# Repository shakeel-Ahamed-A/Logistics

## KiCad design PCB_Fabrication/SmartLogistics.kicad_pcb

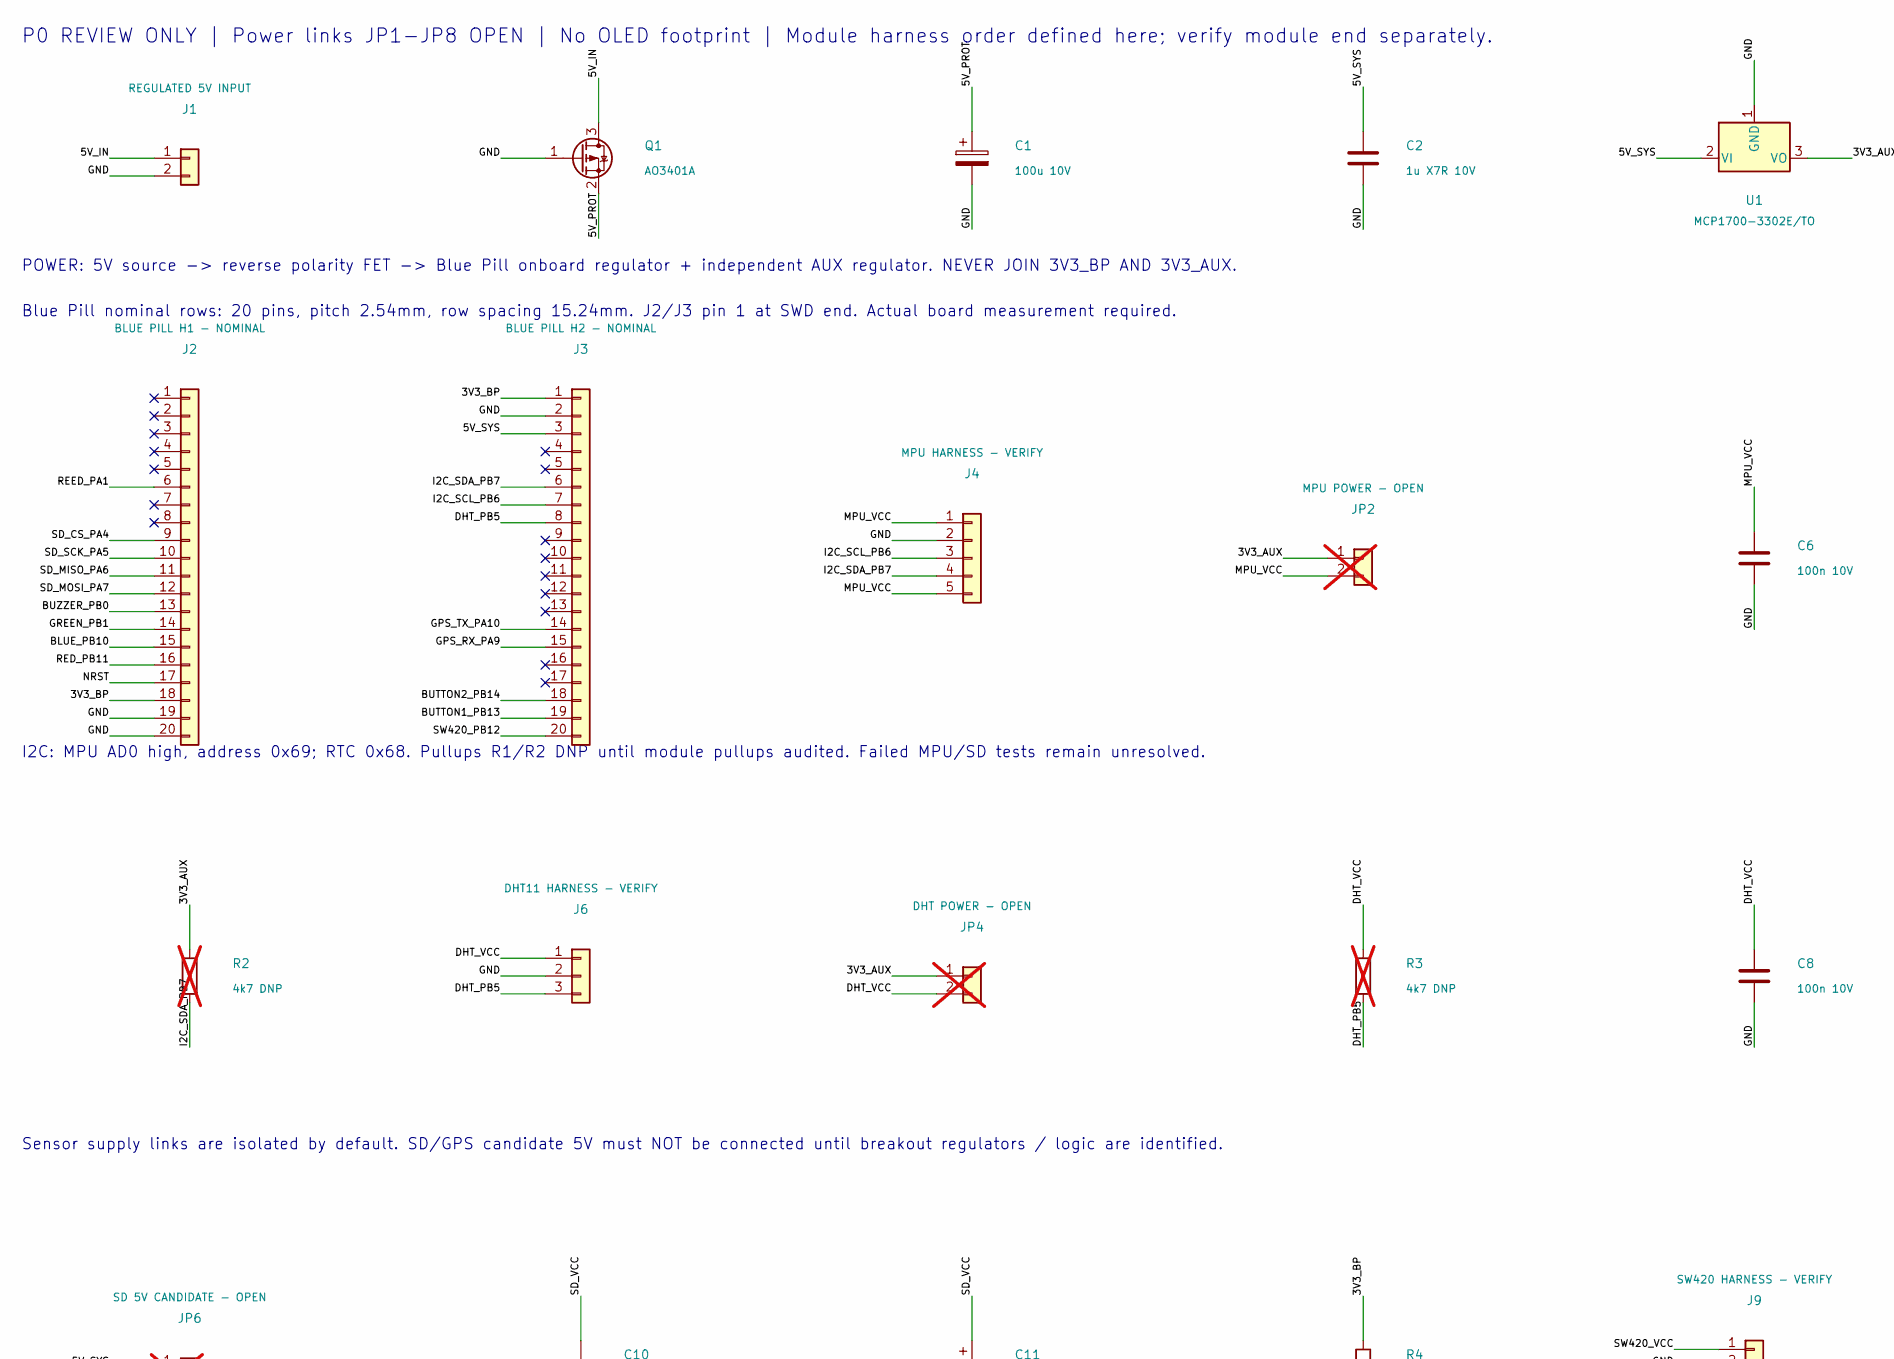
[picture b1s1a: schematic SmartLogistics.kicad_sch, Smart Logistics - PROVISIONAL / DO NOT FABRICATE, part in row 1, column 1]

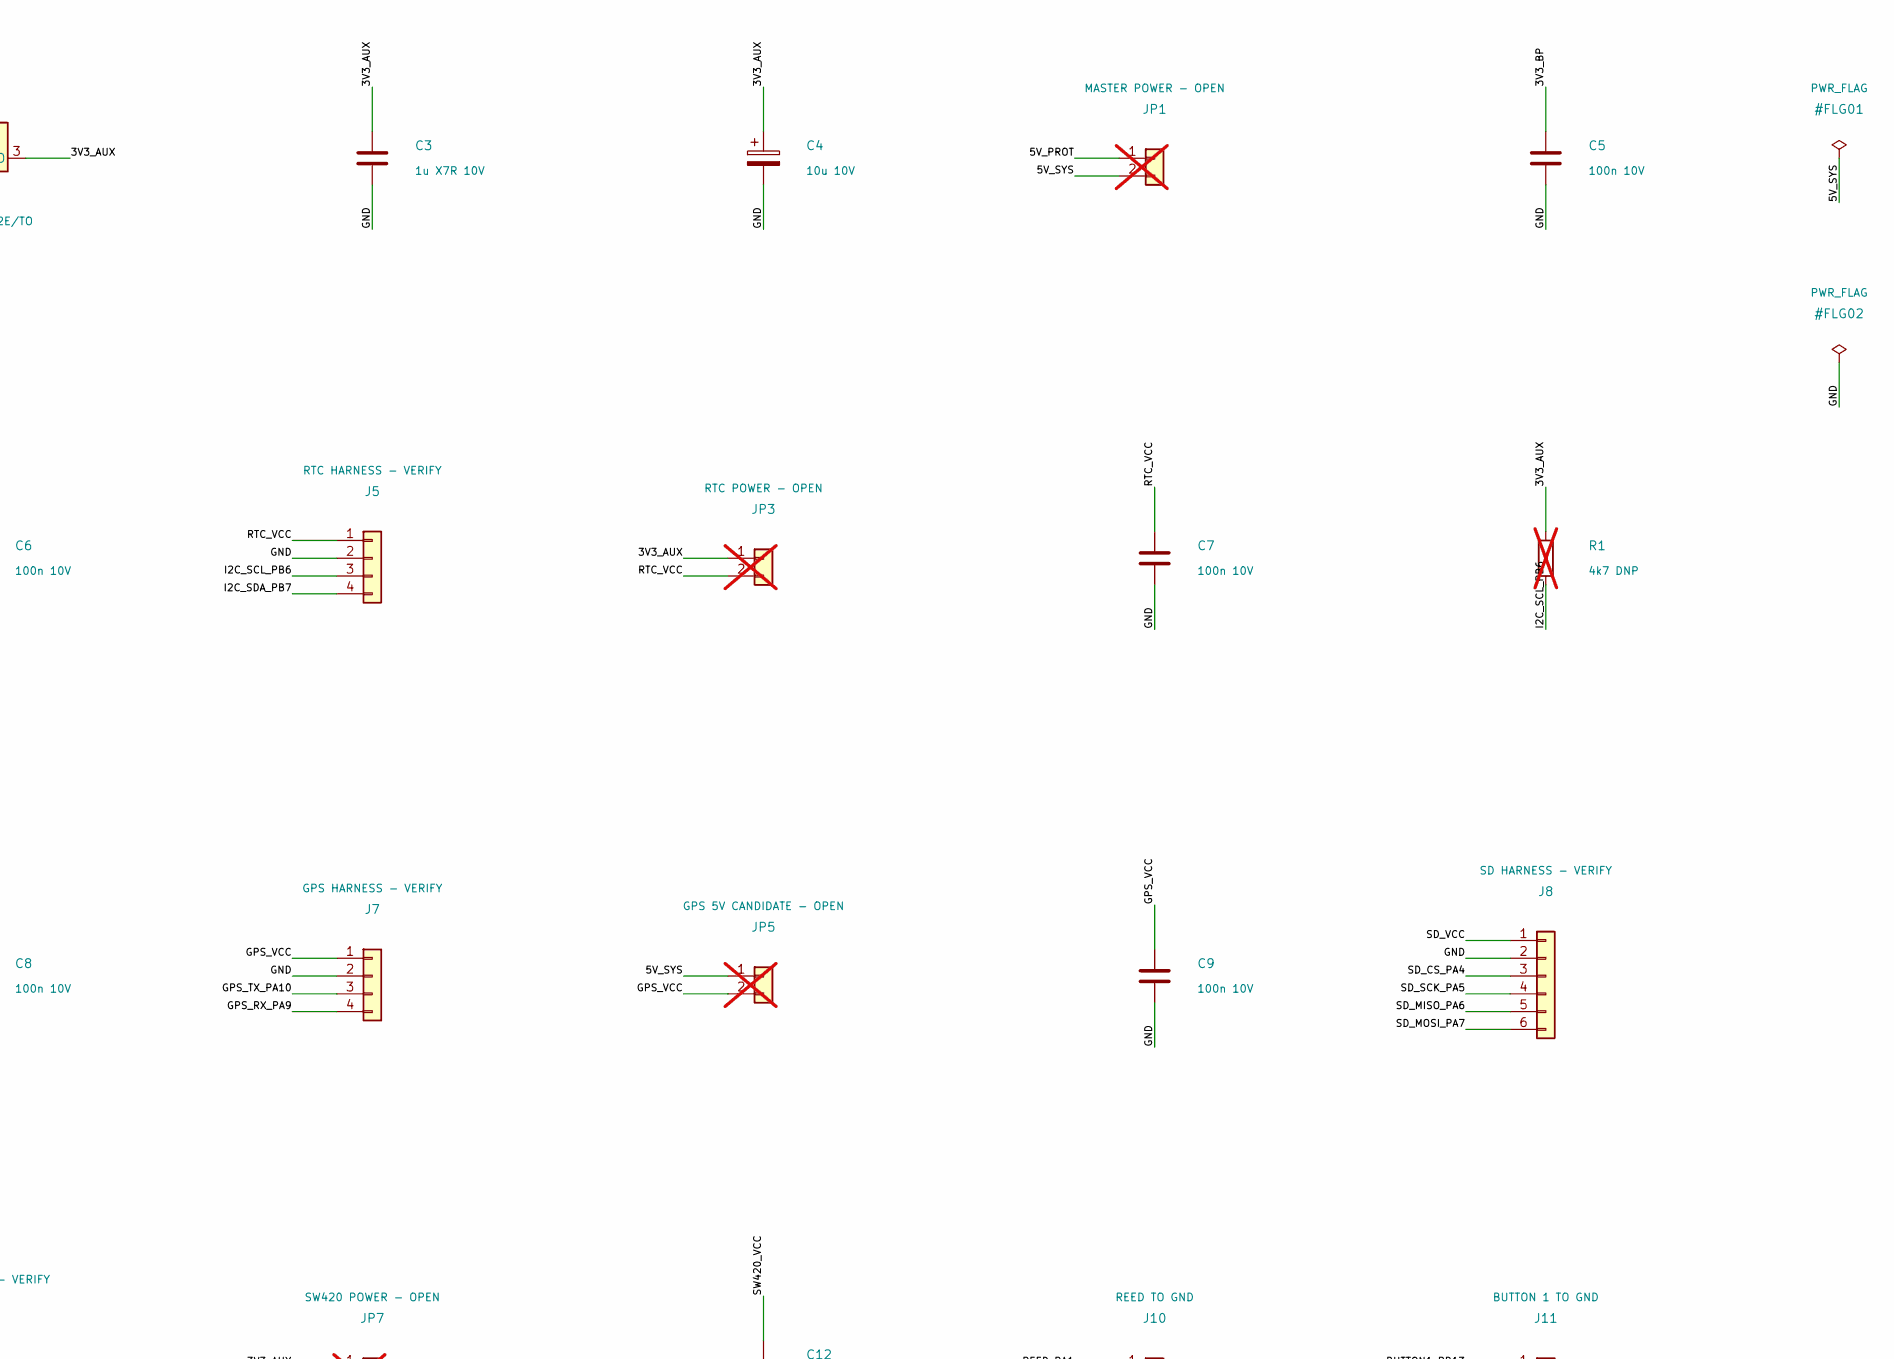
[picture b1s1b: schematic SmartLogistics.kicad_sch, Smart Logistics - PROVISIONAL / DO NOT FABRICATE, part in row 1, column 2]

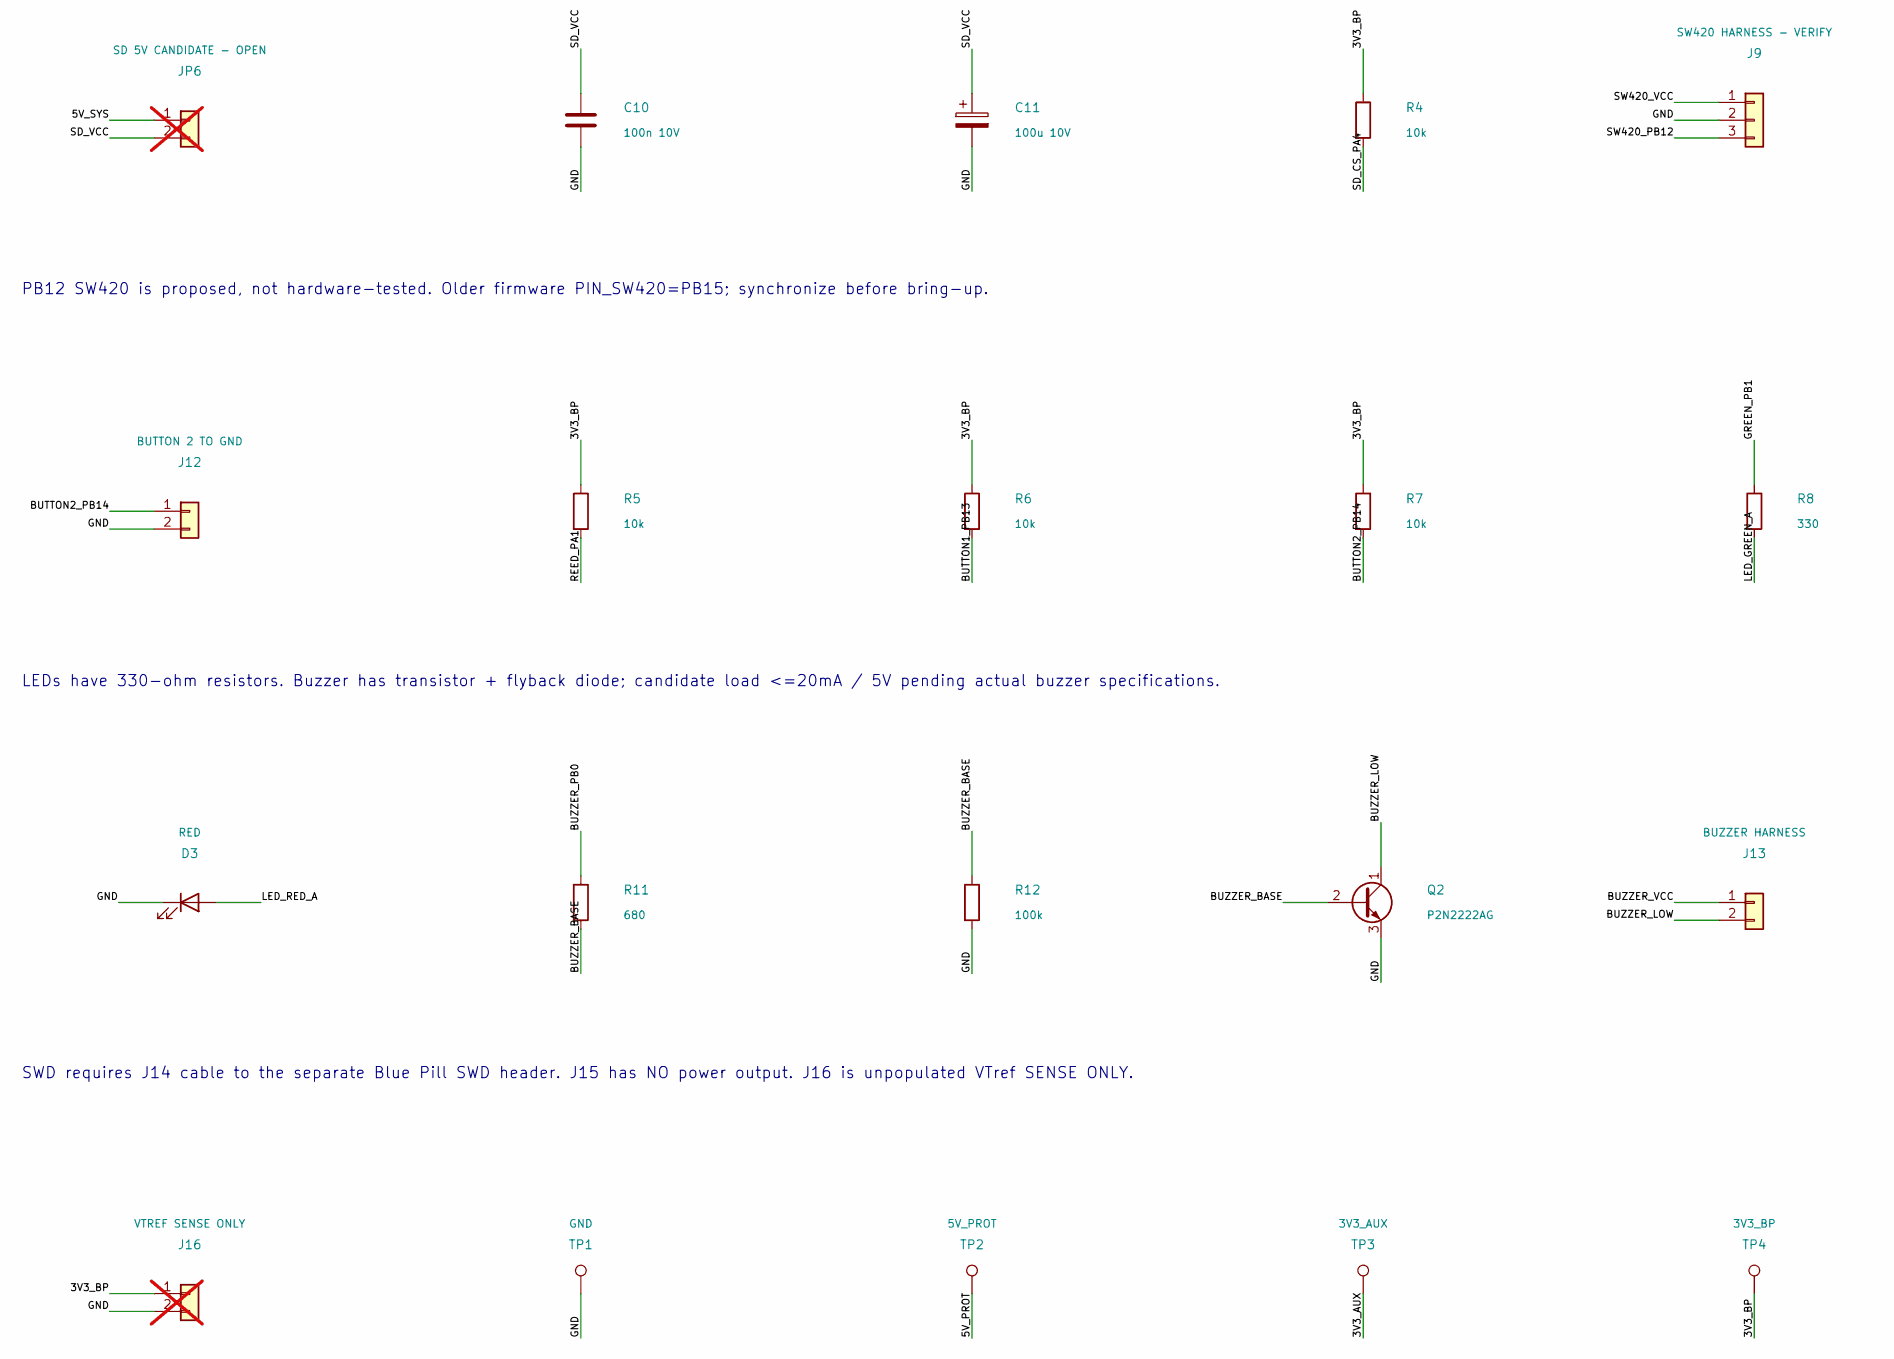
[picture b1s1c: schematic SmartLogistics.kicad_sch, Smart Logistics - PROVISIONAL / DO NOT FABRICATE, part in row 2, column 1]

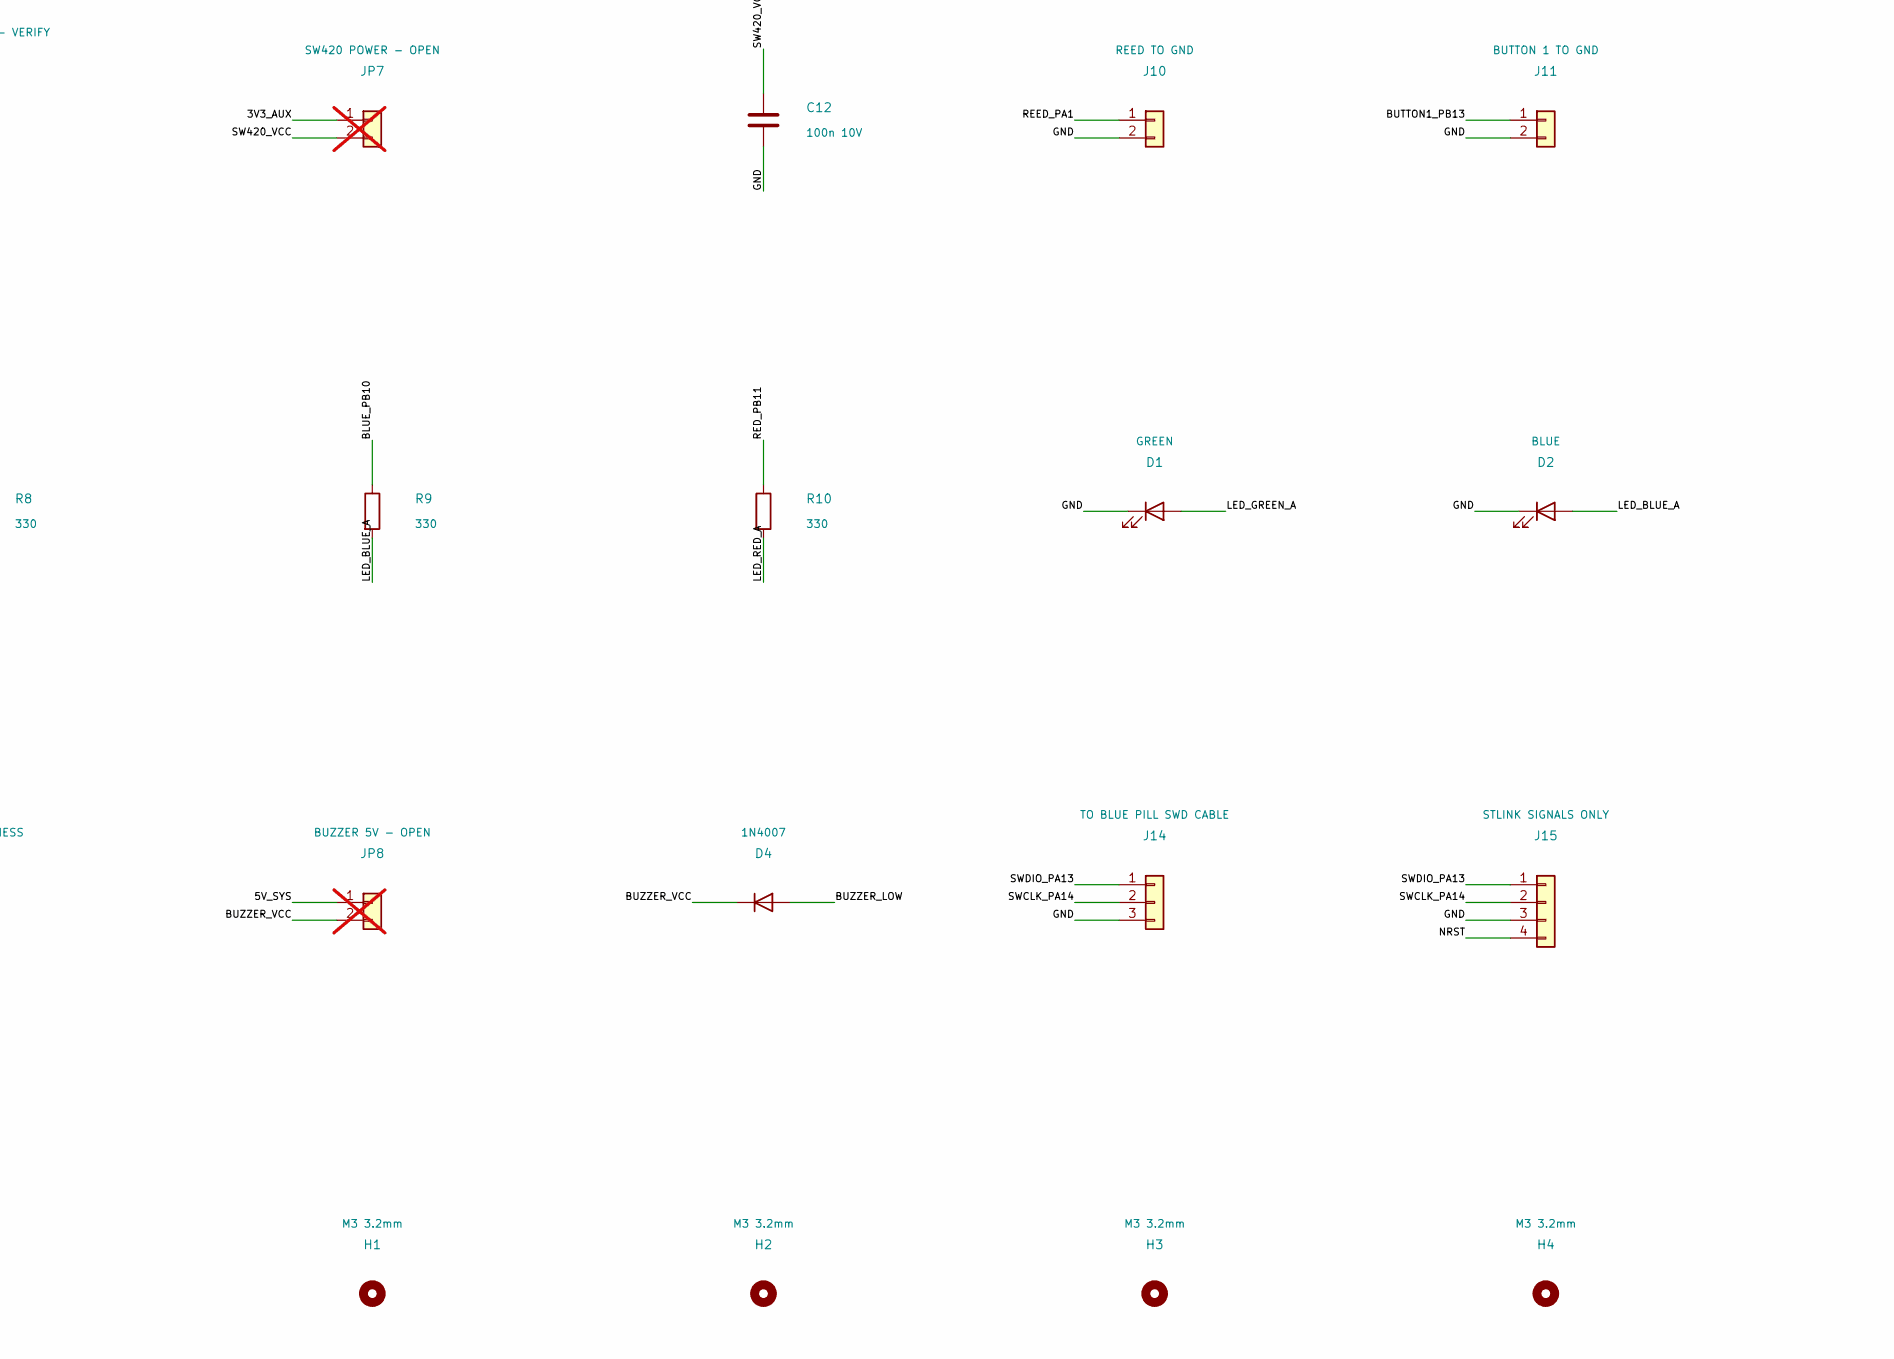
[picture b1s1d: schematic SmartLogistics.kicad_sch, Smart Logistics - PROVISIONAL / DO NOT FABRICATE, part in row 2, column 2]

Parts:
C1, C11: 100u 10V; CP_Radial_D6.3mm_P2.50mm
C2, C3: 1u X7R 10V; C_Disc_D5.0mm_W2.5mm_P5.00mm
C4: 10u 10V; CP_Radial_D6.3mm_P2.50mm
C5, C6, C7, C8, C9, C10, C12: 100n 10V; C_Disc_D5.0mm_W2.5mm_P5.00mm
D1: GREEN; LED_D3.0mm
D2: BLUE; LED_D3.0mm
D3: RED; LED_D3.0mm
D4: 1N4007; D_DO-41_SOD81_P10.16mm_Horizontal
H1, H2, H3, H4: M3 3.2mm; MountingHole_3.2mm_M3
J1: REGULATED 5V INPUT; PinHeader_1x02_P2.54mm_Vertical
J2: BLUE PILL H1 - NOMINAL; PinSocket_1x20_P2.54mm_Vertical
J3: BLUE PILL H2 - NOMINAL; PinSocket_1x20_P2.54mm_Vertical
J4: MPU HARNESS - VERIFY; PinHeader_1x05_P2.54mm_Vertical
J5: RTC HARNESS - VERIFY; PinHeader_1x04_P2.54mm_Vertical
J6: DHT11 HARNESS - VERIFY; PinHeader_1x03_P2.54mm_Vertical
J7: GPS HARNESS - VERIFY; PinHeader_1x04_P2.54mm_Vertical
J8: SD HARNESS - VERIFY; PinHeader_1x06_P2.54mm_Vertical
J9: SW420 HARNESS - VERIFY; PinHeader_1x03_P2.54mm_Vertical
J10: REED TO GND; PinHeader_1x02_P2.54mm_Vertical
J11: BUTTON 1 TO GND; PinHeader_1x02_P2.54mm_Vertical
J12: BUTTON 2 TO GND; PinHeader_1x02_P2.54mm_Vertical
J13: BUZZER HARNESS; PinHeader_1x02_P2.54mm_Vertical
J14: TO BLUE PILL SWD CABLE; PinHeader_1x03_P2.54mm_Vertical
J15: STLINK SIGNALS ONLY; PinHeader_1x04_P2.54mm_Vertical
J16: VTREF SENSE ONLY; PinHeader_1x02_P2.54mm_Vertical; not fitted
JP1: MASTER POWER - OPEN; PinHeader_1x02_P2.54mm_Vertical; not fitted
JP2: MPU POWER - OPEN; PinHeader_1x02_P2.54mm_Vertical; not fitted
JP3: RTC POWER - OPEN; PinHeader_1x02_P2.54mm_Vertical; not fitted
JP4: DHT POWER - OPEN; PinHeader_1x02_P2.54mm_Vertical; not fitted
JP5: GPS 5V CANDIDATE - OPEN; PinHeader_1x02_P2.54mm_Vertical; not fitted
JP6: SD 5V CANDIDATE - OPEN; PinHeader_1x02_P2.54mm_Vertical; not fitted
JP7: SW420 POWER - OPEN; PinHeader_1x02_P2.54mm_Vertical; not fitted
JP8: BUZZER 5V - OPEN; PinHeader_1x02_P2.54mm_Vertical; not fitted
Q1: AO3401A; SOT-23
Q2: P2N2222AG; TO-92_Inline_Wide
R1, R2, R3: 4k7 DNP; R_Axial_DIN0207_L6.3mm_D2.5mm_P10.16mm_Horizontal; not fitted
R4, R5, R6, R7: 10k; R_Axial_DIN0207_L6.3mm_D2.5mm_P10.16mm_Horizontal
R8, R9, R10: 330; R_Axial_DIN0207_L6.3mm_D2.5mm_P10.16mm_Horizontal
R11: 680; R_Axial_DIN0207_L6.3mm_D2.5mm_P10.16mm_Horizontal
R12: 100k; R_Axial_DIN0207_L6.3mm_D2.5mm_P10.16mm_Horizontal
TP1: GND; TestPoint_THTPad_D2.0mm_Drill1.0mm
TP2: 5V_PROT; TestPoint_THTPad_D2.0mm_Drill1.0mm
TP3: 3V3_AUX; TestPoint_THTPad_D2.0mm_Drill1.0mm
TP4: 3V3_BP; TestPoint_THTPad_D2.0mm_Drill1.0mm
U1: MCP1700-3302E/TO; TO-92_Inline_Wide

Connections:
/3V3_AUX: C3.1, C4.1, JP2.1, JP3.1, JP4.1, JP7.1, R1.1, R2.1, TP3.1, U1.3 (VO)
/3V3_BP: C5.1, J2.18, J3.1, J16.1, R4.1, R5.1, R6.1, R7.1, TP4.1
/5V_IN: J1.1, Q1.3 (D)
/5V_PROT: C1.1, JP1.1, Q1.2 (S), TP2.1
/5V_SYS: C2.1, J3.3, JP1.2, JP5.1, JP6.1, JP8.1, U1.2 (VI)
/BLUE_PB10: J2.15, R9.1
/BUTTON1_PB13: J3.19, J11.1, R6.2
/BUTTON2_PB14: J3.18, J12.1, R7.2
/BUZZER_BASE: Q2.2 (B), R11.2, R12.1
/BUZZER_LOW: D4.2 (A), J13.2, Q2.1 (C)
/BUZZER_PB0: J2.13, R11.1
/BUZZER_VCC: D4.1 (K), J13.1, JP8.2
/DHT_PB5: J3.8, J6.3, R3.2
/DHT_VCC: C8.1, J6.1, JP4.2, R3.1
/GND: C1.2, C2.2, C3.2, C4.2, C5.2, C6.2, C7.2, C8.2, C9.2, C10.2, C11.2, C12.2, D1.1 (K), D2.1 (K), D3.1 (K), J1.2, J2.19, J2.20, J3.2, J4.2, J5.2, J6.2, J7.2, J8.2, J9.2, J10.2, J11.2, J12.2, J14.3, J15.3, J16.2, Q1.1 (G), Q2.3 (E), R12.2, TP1.1, U1.1 (GND)
/GPS_RX_PA9: J3.15, J7.4
/GPS_TX_PA10: J3.14, J7.3
/GPS_VCC: C9.1, J7.1, JP5.2
/GREEN_PB1: J2.14, R8.1
/I2C_SCL_PB6: J3.7, J4.3, J5.3, R1.2
/I2C_SDA_PB7: J3.6, J4.4, J5.4, R2.2
/LED_BLUE_A: D2.2 (A), R9.2
/LED_GREEN_A: D1.2 (A), R8.2
/LED_RED_A: D3.2 (A), R10.2
/MPU_VCC: C6.1, J4.1, J4.5, JP2.2
/NRST: J2.17, J15.4
/RED_PB11: J2.16, R10.1
/REED_PA1: J2.6, J10.1, R5.2
/RTC_VCC: C7.1, J5.1, JP3.2
/SD_CS_PA4: J2.9, J8.3, R4.2
/SD_MISO_PA6: J2.11, J8.5
/SD_MOSI_PA7: J2.12, J8.6
/SD_SCK_PA5: J2.10, J8.4
/SD_VCC: C10.1, C11.1, J8.1, JP6.2
/SW420_PB12: J3.20, J9.3
/SW420_VCC: C12.1, J9.1, JP7.2
/SWCLK_PA14: J14.2, J15.2
/SWDIO_PA13: J14.1, J15.1

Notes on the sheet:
P0 REVIEW ONLY | Power links JP1-JP8 OPEN | No OLED footprint | Module harness order defined here; verify module end separately.
POWER: 5V source -> reverse polarity FET -> Blue Pill onboard regulator + independent AUX regulator. NEVER JOIN 3V3_BP AND 3V3_AUX.
Blue Pill nominal rows: 20 pins, pitch 2.54mm, row spacing 15.24mm. J2/J3 pin 1 at SWD end. Actual board measurement required.
I2C: MPU AD0 high, address 0x69; RTC 0x68. Pullups R1/R2 DNP until module pullups audited. Failed MPU/SD tests remain unresolved.
Sensor supply links are isolated by default. SD/GPS candidate 5V must NOT be connected until breakout regulators / logic are identified.
PB12 SW420 is proposed, not hardware-tested. Older firmware PIN_SW420=PB15; synchronize before bring-up.
LEDs have 330-ohm resistors. Buzzer has transistor + flyback diode; candidate load <=20mA / 5V pending actual buzzer specifications.
SWD requires J14 cable to the separate Blue Pill SWD header. J15 has NO power output. J16 is unpopulated VTref SENSE ONLY.

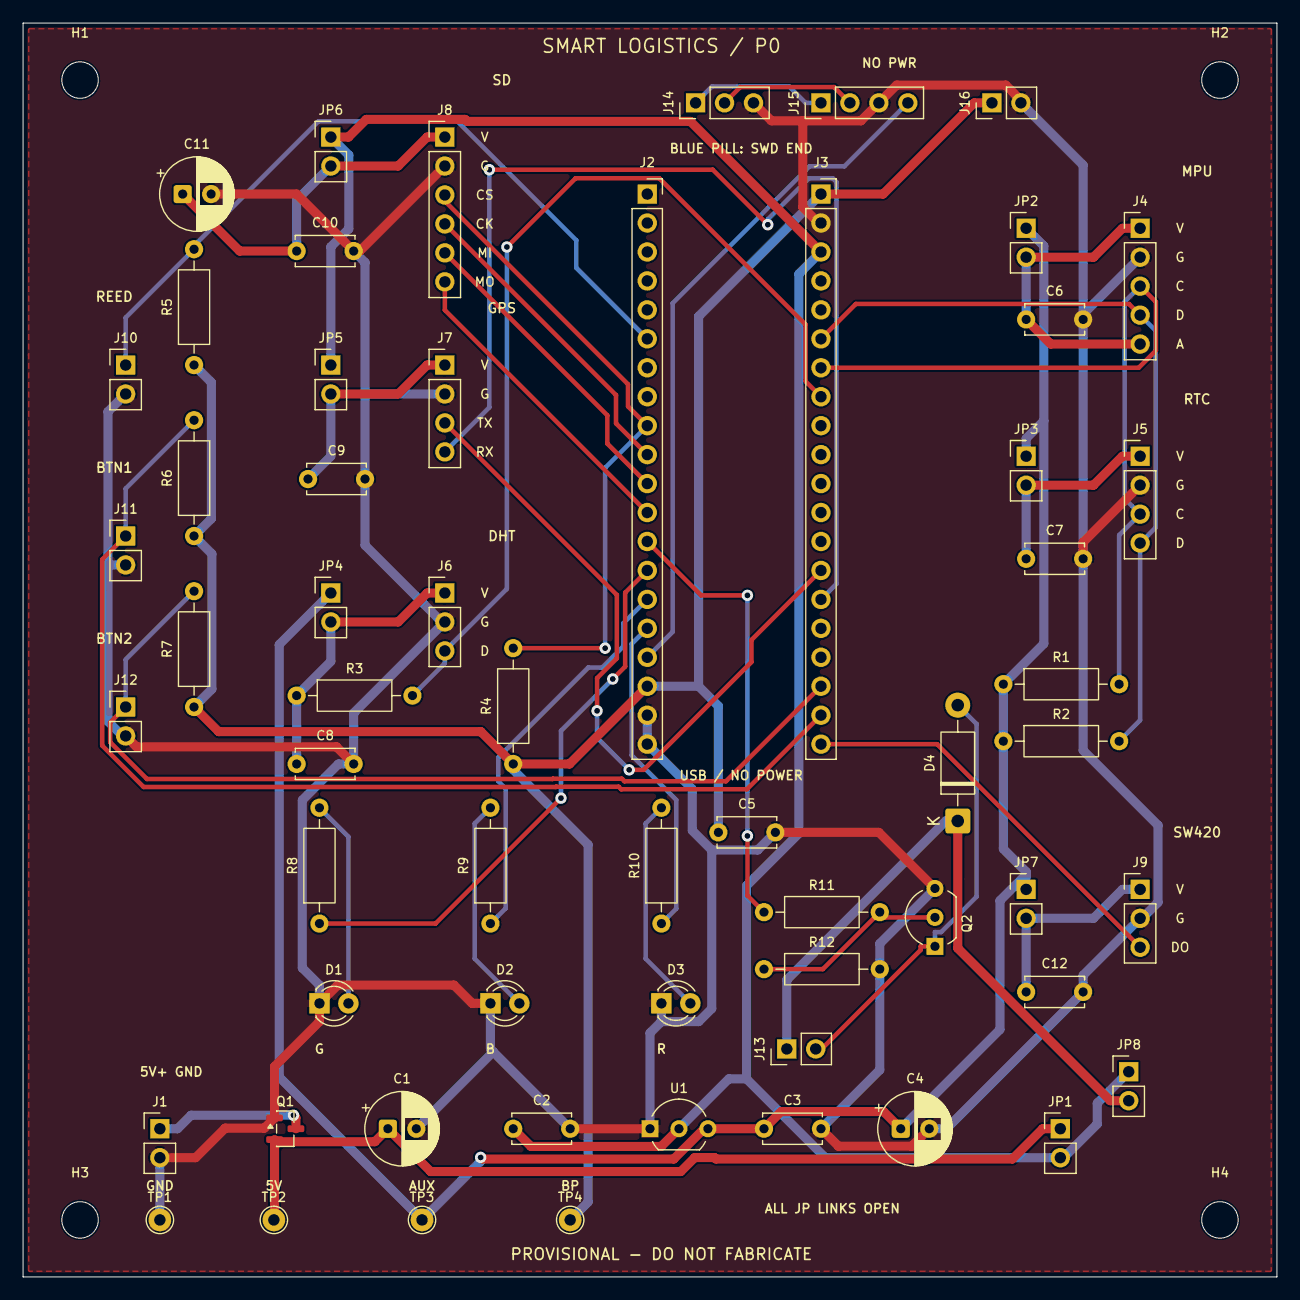
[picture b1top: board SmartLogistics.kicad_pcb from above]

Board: 2 copper layers, 110.0 x 110.0 mm, 63 parts (0 on the bottom side), 38 nets.

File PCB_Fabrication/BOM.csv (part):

Reference,Value_or_candidate_part,Quantity,Footprint,Populate,Status,Notes
J1,REGULATED 5V INPUT,1,Carrier:PinHeader_1x02_P2.54mm_Vertical,PROVISIONAL,NOT PURCHASE/ASSEMBLY APPROVED,"5V +/-5%, current-limited source >=1A required; not presently available"
Q1,AO3401A,1,Carrier:SOT-23,PROVISIONAL,NOT PURCHASE/ASSEMBLY APPROVED,"Candidate reverse-polarity MOSFET: G1 S2 D3; drain input, source output. Does not block reverse current from another supply."
C1,100u 10V,1,Carrier:CP_Radial_D6.3mm_P2.50mm,PROVISIONAL,NOT PURCHASE/ASSEMBLY APPROVED,
C2,1u X7R 10V,1,Carrier:C_Disc_D5.0mm_W2.5mm_P5.00mm,PROVISIONAL,NOT PURCHASE/ASSEMBLY APPROVED,
U1,MCP1700-3302E/TO,1,Carrier:TO-92_Inline_Wide,PROVISIONAL,NOT PURCHASE/ASSEMBLY APPROVED,New candidate AUX-only LDO; 150mA design ceiling pending final loads and thermal validation
C3,1u X7R 10V,1,Carrier:C_Disc_D5.0mm_W2.5mm_P5.00mm,PROVISIONAL,NOT PURCHASE/ASSEMBLY APPROVED,
C4,10u 10V,1,Carrier:CP_Radial_D6.3mm_P2.50mm,PROVISIONAL,NOT PURCHASE/ASSEMBLY APPROVED,
JP1,MASTER POWER - OPEN,1,Carrier:PinHeader_1x02_P2.54mm_Vertical,NO / OPEN,NOT PURCHASE/ASSEMBLY APPROVED,Fit only after identifying Blue Pill regulator. No USB or ST-LINK power while connected.
C5,100n 10V,1,Carrier:C_Disc_D5.0mm_W2.5mm_P5.00mm,PROVISIONAL,NOT PURCHASE/ASSEMBLY APPROVED,
J2,BLUE PILL H1 - NOMINAL,1,Carrier:PinSocket_1x20_P2.54mm_Vertical,PROVISIONAL,NOT PURCHASE/ASSEMBLY APPROVED,20x2.54; pin1=VBAT at SWD end. User physical fit and orientation UNVERIFIED.
J3,BLUE PILL H2 - NOMINAL,1,Carrier:PinSocket_1x20_P2.54mm_Vertical,PROVISIONAL,NOT PURCHASE/ASSEMBLY APPROVED,15.24mm from H1 nominal. Pin1=3V3 at SWD end. No carrier AUX rail connection.
J4,MPU HARNESS - VERIFY,1,Carrier:PinHeader_1x05_P2.54mm_Vertical,PROVISIONAL,NOT PURCHASE/ASSEMBLY APPROVED,"Harness 1=VCC,2=GND,3=SCL,4=SDA,5=AD0. AD0=MPU_VCC (candidate 3.3V). Verify actual MPU core/VLOGIC before enabling. No plug-in footprint claimed."
JP2,MPU POWER - OPEN,1,Carrier:PinHeader_1x02_P2.54mm_Vertical,NO / OPEN,NOT PURCHASE/ASSEMBLY APPROVED,
C6,100n 10V,1,Carrier:C_Disc_D5.0mm_W2.5mm_P5.00mm,PROVISIONAL,NOT PURCHASE/ASSEMBLY APPROVED,
J5,RTC HARNESS - VERIFY,1,Carrier:PinHeader_1x04_P2.54mm_Vertical,PROVISIONAL,NOT PURCHASE/ASSEMBLY APPROVED,Remove/disable any battery charger before a CR2032 is fitted. Verify onboard I2C pullups and battery holder underside clearance.
JP3,RTC POWER - OPEN,1,Carrier:PinHeader_1x02_P2.54mm_Vertical,NO / OPEN,NOT PURCHASE/ASSEMBLY APPROVED,
C7,100n 10V,1,Carrier:C_Disc_D5.0mm_W2.5mm_P5.00mm,PROVISIONAL,NOT PURCHASE/ASSEMBLY APPROVED,
R1,4k7 DNP,1,Carrier:R_Axial_DIN0207_L6.3mm_D2.5mm_P10.16mm_Horizontal,NO / OPEN,NOT PURCHASE/ASSEMBLY APPROVED,Populate only if combined module pullups require it
R2,4k7 DNP,1,Carrier:R_Axial_DIN0207_L6.3mm_D2.5mm_P10.16mm_Horizontal,NO / OPEN,NOT PURCHASE/ASSEMBLY APPROVED,
J6,DHT11 HARNESS - VERIFY,1,Carrier:PinHeader_1x03_P2.54mm_Vertical,PROVISIONAL,NOT PURCHASE/ASSEMBLY APPROVED,3-pin module; verify actual pin order. 3.3V operation and module pullup destination pending.
JP4,DHT POWER - OPEN,1,Carrier:PinHeader_1x02_P2.54mm_Vertical,NO / OPEN,NOT PURCHASE/ASSEMBLY APPROVED,
R3,4k7 DNP,1,Carrier:R_Axial_DIN0207_L6.3mm_D2.5mm_P10.16mm_Horizontal,NO / OPEN,NOT PURCHASE/ASSEMBLY APPROVED,
C8,100n 10V,1,Carrier:C_Disc_D5.0mm_W2.5mm_P5.00mm,PROVISIONAL,NOT PURCHASE/ASSEMBLY APPROVED,
J7,GPS HARNESS - VERIFY,1,Carrier:PinHeader_1x04_P2.54mm_Vertical,PROVISIONAL,NOT PURCHASE/ASSEMBLY APPROVED,3=GPS TX to MCU RX;4=GPS RX from MCU TX. 5V applies only if actual BREAKOUT input regulator is verified; never bare NEO-6M VCC.
JP5,GPS 5V CANDIDATE - OPEN,1,Carrier:PinHeader_1x02_P2.54mm_Vertical,NO / OPEN,NOT PURCHASE/ASSEMBLY APPROVED,
C9,100n 10V,1,Carrier:C_Disc_D5.0mm_W2.5mm_P5.00mm,PROVISIONAL,NOT PURCHASE/ASSEMBLY APPROVED,
J8,SD HARNESS - VERIFY,1,Carrier:PinHeader_1x06_P2.54mm_Vertical,PROVISIONAL,NOT PURCHASE/ASSEMBLY APPROVED,6-pin blue adapter. Candidate power is isolated. Buffer VIH/VIL and MISO voltage not verified. SPI traces provisional; do not energize until audited.
JP6,SD 5V CANDIDATE - OPEN,1,Carrier:PinHeader_1x02_P2.54mm_Vertical,NO / OPEN,NOT PURCHASE/ASSEMBLY APPROVED,
C10,100n 10V,1,Carrier:C_Disc_D5.0mm_W2.5mm_P5.00mm,PROVISIONAL,NOT PURCHASE/ASSEMBLY APPROVED,
C11,100u 10V,1,Carrier:CP_Radial_D6.3mm_P2.50mm,PROVISIONAL,NOT PURCHASE/ASSEMBLY APPROVED,
R4,10k,1,Carrier:R_Axial_DIN0207_L6.3mm_D2.5mm_P10.16mm_Horizontal,PROVISIONAL,NOT PURCHASE/ASSEMBLY APPROVED,
J9,SW420 HARNESS - VERIFY,1,Carrier:PinHeader_1x03_P2.54mm_Vertical,PROVISIONAL,NOT PURCHASE/ASSEMBLY APPROVED,PB12 is proposed only; firmware previously PB15. Verify comparator operation and output pullup at 3.3V.
JP7,SW420 POWER - OPEN,1,Carrier:PinHeader_1x02_P2.54mm_Vertical,NO / OPEN,NOT PURCHASE/ASSEMBLY APPROVED,
C12,100n 10V,1,Carrier:C_Disc_D5.0mm_W2.5mm_P5.00mm,PROVISIONAL,NOT PURCHASE/ASSEMBLY APPROVED,
J10,REED TO GND,1,Carrier:PinHeader_1x02_P2.54mm_Vertical,PROVISIONAL,NOT PURCHASE/ASSEMBLY APPROVED,
J11,BUTTON 1 TO GND,1,Carrier:PinHeader_1x02_P2.54mm_Vertical,PROVISIONAL,NOT PURCHASE/ASSEMBLY APPROVED,
J12,BUTTON 2 TO GND,1,Carrier:PinHeader_1x02_P2.54mm_Vertical,PROVISIONAL,NOT PURCHASE/ASSEMBLY APPROVED,
R5,10k,1,Carrier:R_Axial_DIN0207_L6.3mm_D2.5mm_P10.16mm_Horizontal,PROVISIONAL,NOT PURCHASE/ASSEMBLY APPROVED,
R6,10k,1,Carrier:R_Axial_DIN0207_L6.3mm_D2.5mm_P10.16mm_Horizontal,PROVISIONAL,NOT PURCHASE/ASSEMBLY APPROVED,
R7,10k,1,Carrier:R_Axial_DIN0207_L6.3mm_D2.5mm_P10.16mm_Horizontal,PROVISIONAL,NOT PURCHASE/ASSEMBLY APPROVED,
R8,330,1,Carrier:R_Axial_DIN0207_L6.3mm_D2.5mm_P10.16mm_Horizontal,PROVISIONAL,NOT PURCHASE/ASSEMBLY APPROVED,
D1,GREEN,1,Carrier:LED_D3.0mm,PROVISIONAL,NOT PURCHASE/ASSEMBLY APPROVED,Candidate 3mm LED; pin1 cathode. Verify chosen LED forward voltage/brightness.
R9,330,1,Carrier:R_Axial_DIN0207_L6.3mm_D2.5mm_P10.16mm_Horizontal,PROVISIONAL,NOT PURCHASE/ASSEMBLY APPROVED,
D2,BLUE,1,Carrier:LED_D3.0mm,PROVISIONAL,NOT PURCHASE/ASSEMBLY APPROVED,Candidate 3mm LED; pin1 cathode. Verify chosen LED forward voltage/brightness.
R10,330,1,Carrier:R_Axial_DIN0207_L6.3mm_D2.5mm_P10.16mm_Horizontal,PROVISIONAL,NOT PURCHASE/ASSEMBLY APPROVED,
D3,RED,1,Carrier:LED_D3.0mm,PROVISIONAL,NOT PURCHASE/ASSEMBLY APPROVED,Candidate 3mm LED; pin1 cathode. Verify chosen LED forward voltage/brightness.
R11,680,1,Carrier:R_Axial_DIN0207_L6.3mm_D2.5mm_P10.16mm_Horizontal,PROVISIONAL,NOT PURCHASE/ASSEMBLY APPROVED,
R12,100k,1,Carrier:R_Axial_DIN0207_L6.3mm_D2.5mm_P10.16mm_Horizontal,PROVISIONAL,NOT PURCHASE/ASSEMBLY APPROVED,
Q2,P2N2222AG,1,Carrier:TO-92_Inline_Wide,PROVISIONAL,NOT PURCHASE/ASSEMBLY APPROVED,"Candidate onsemi P2N2222AG C1 B2 E3, not arbitrary 2N2222 substitute. Proposed load <=20mA, verify actual buzzer before fitting link."
J13,BUZZER HARNESS,1,Carrier:PinHeader_1x02_P2.54mm_Vertical,PROVISIONAL,NOT PURCHASE/ASSEMBLY APPROVED,
JP8,BUZZER 5V - OPEN,1,Carrier:PinHeader_1x02_P2.54mm_Vertical,NO / OPEN,NOT PURCHASE/ASSEMBLY APPROVED,
D4,1N4007,1,Carrier:D_DO-41_SOD81_P10.16mm_Horizontal,PROVISIONAL,NOT PURCHASE/ASSEMBLY APPROVED,Flyback cathode pin1 to + buzzer supply. Validate acoustic behavior for passive buzzer.
J14,TO BLUE PILL SWD CABLE,1,Carrier:PinHeader_1x03_P2.54mm_Vertical,PROVISIONAL,NOT PURCHASE/ASSEMBLY APPROVED,Short cable to existing separate Blue Pill SWD header. Carrier order is NOT Blue Pill 4-pin order. Do not wire its 3.3V power pin.
J15,STLINK SIGNALS ONLY,1,Carrier:PinHeader_1x04_P2.54mm_Vertical,PROVISIONAL,NOT PURCHASE/ASSEMBLY APPROVED,No programmer power. Power target externally before connecting signals. Identify debugger model.
J16,VTREF SENSE ONLY,1,Carrier:PinHeader_1x02_P2.54mm_Vertical,NO / OPEN,NOT PURCHASE/ASSEMBLY APPROVED,For verified genuine debugger VTref input only. Never connect clone 3.3V output. Leave unpopulated by default.
TP1,GND,1,Carrier:TestPoint_THTPad_D2.0mm_Drill1.0mm,PROVISIONAL,NOT PURCHASE/ASSEMBLY APPROVED,
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
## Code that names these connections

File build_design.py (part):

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cap('C7','100n 10V','RTC_VCC',(615,125),(108,62,0),'SENSORS')
resistor('R1','4k7 DNP','3V3_AUX','I2C_SCL_PB6',(695,125),(106,73,0),'SENSORS',True,'Populate only if combined module pullups require it')
resistor('R2','4k7 DNP','3V3_AUX','I2C_SDA_PB7',(55,210),(106,78,0),'SENSORS',True)
conn('J6','DHT11 HARNESS - VERIFY',['DHT_VCC','GND','DHT_PB5'],(135,210),(57,65,0),'SENSORS',notes='3-pin module; verify actual pin order. 3.3V operation and module pullup destination pending.')
conn('JP4','DHT POWER - OPEN',['3V3_AUX','DHT_VCC'],(215,210),(47,65,0),'SENSORS',True)
resistor('R3','4k7 DNP','DHT_VCC','DHT_PB5',(295,210),(44,74,0),'SENSORS',True)
cap('C8','100n 10V','DHT_VCC',(375,210),(44,80,0),'SENSORS')
conn('J7','GPS HARNESS - VERIFY',['GPS_VCC','GND','GPS_TX_PA10','GPS_RX_PA9'],(455,210),(57,45,0),'SENSORS',notes='3=GPS TX to MCU RX;4=GPS RX from MCU TX. 5V applies only if actual BREAKOUT input regulator is verified; never bare NEO-6M VCC.')
conn('JP5','GPS 5V CANDIDATE - OPEN',['5V_SYS','GPS_VCC'],(535,210),(47,45,0),'SENSORS',True)
cap('C9','100n 10V','GPS_VCC',(615,210),(45,55,0),'SENSORS')
conn('J8','SD HARNESS - VERIFY',['SD_VCC','GND','SD_CS_PA4','SD_SCK_PA5','SD_MISO_PA6','SD_MOSI_PA7'],(695,210),(57,25,0),'SENSORS',notes='6-pin blue adapter. Candidate power is isolated. Buffer VIH/VIL and MISO voltage not verified. SPI traces provisional; do not energize until audited.')
conn('JP6','SD 5V CANDIDATE - OPEN',['5V_SYS','SD_VCC'],(55,290),(47,25,0),'SENSORS',True)
cap('C10','100n 10V','SD_VCC',(135,290),(44,35,0),'SENSORS')
cap('C11','100u 10V','SD_VCC',(215,290),(34,30,0),'SENSORS',True)
resistor('R4','10k','3V3_BP','SD_CS_PA4',(295,290),(61,84,0),'SENSORS')
conn('J9','SW420 HARNESS - VERIFY',['SW420_VCC','GND','SW420_PB12'],(375,290),(118,91,0),'SENSORS',notes='PB12 is proposed only; firmware previously PB15. Verify comparator operation and output pullup at 3.3V.')
conn('JP7','SW420 POWER - OPEN',['3V3_AUX','SW420_VCC'],(455,290),(108,91,0),'SENSORS',True)
cap('C12','100n 10V','SW420_VCC',(535,290),(108,100,0),'SENSORS')
conn('J10','REED TO GND',['REED_PA1','GND'],(615,290),(29,45,0),'CONTROLS')
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conn('J13','BUZZER HARNESS',['BUZZER_VCC','BUZZER_LOW'],(375,450),(91,103,0),'BUZZER')
conn('JP8','BUZZER 5V - OPEN',['5V_SYS','BUZZER_VCC'],(455,450),(101,106,0),'BUZZER',True)
add('D4','Device','D','1N4007',{1:'BUZZER_VCC',2:'BUZZER_LOW'},(535,450),(102,85,90),'Diode_THT:D_DO-41_SOD81_P10.16mm_Horizontal','BUZZER',notes='Flyback cathode pin1 to + buzzer supply. Validate acoustic behavior for passive buzzer.')
conn('J14','TO BLUE PILL SWD CABLE',['SWDIO_PA13','SWCLK_PA14','GND'],(615,450),(79,22,90),'PROGRAMMING',notes='Short cable to existing separate Blue Pill SWD header. Carrier order is NOT Blue Pill 4-pin order. Do not wire its 3.3V power pin.')
conn('J15','STLINK SIGNALS ONLY',['SWDIO_PA13','SWCLK_PA14','GND','NRST'],(695,450),(90,22,90),'PROGRAMMING',notes='No programmer power. Power target externally before connecting signals. Identify debugger model.')
conn('J16','VTREF SENSE ONLY',['3V3_BP','GND'],(55,530),(105,22,90),'PROGRAMMING',True,'For verified genuine debugger VTref input only. Never connect clone 3.3V output. Leave unpopulated by default.')
for i,(net,px) in enumerate([('GND',32),('5V_PROT',42),('3V3_AUX',55),('3V3_BP',68)]):
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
